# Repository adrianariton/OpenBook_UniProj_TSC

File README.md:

# Ariton Adrian TSC - proiect

# Implementation Steps

1. **Schematic Creation**
2. **Push to 2D PCB**
3. **Routing**
   - GND plane  
   - Net Class for Power Trails  
   - Custom rules & constraints upload  
   - Routing
4. **3D Models Design from Datasheets**
   - Battery  
   - Screen

---

# Hardware Modules and Components

## ESP32-C6-WROOM-1-N8 – Main Microcontroller
- WiFi 6, Bluetooth 5 LE, RISC-V core  
- Power Supply: 3.3V  
- Communications: SPI, I2C, UART, GPIO  

## SD Card Module
- Interface: SPI  
- Pins Used:
  - `SS_SD` → IO4  
  - `MOSI` → IO7  
  - `MISO` → IO2  
  - `SCK` → IO6  

## E-Paper Display
- Interface: SPI  
- Pins Used:
  - `EPD_CS` → IO10  
  - `EPD_DC` → IO5  
  - `EPD_RST` → IO23  
  - `EPD_BUSY` → IO3 (shared with MISO)  
  - MOSI, SCK (shared with SD)

## RTC Module - DS3231SN
- Interface: I2C  
- Pins Used:
  - `SCL` → IO22  
  - `SDA` → IO21  
  - `INT_RTC` → IO8  
  - `32KHZ` → IO1  
  - `RTC_RST` → IO18  

## Environmental Sensor - BME688
- Interface: I2C (shared with RTC)  
- Power Supply: 3.3V  

## External Flash - NORFlash64MB
- Interface: SPI  
- Pins Used:
  - `FLASH_CS` → IO12  
  - Rest (MOSI, MISO, SCK) shared  

## SD/USB Interface
- `USB_D+` → IO13  
- `USB_D-` → IO12  

## Reset and Boot Buttons
- `IO/BOOT` → IO9  
- `RESET` → EN  

## Li-Po Battery Charging Controller
- TP4056 or similar  
- Built-in charging control  
- Battery level monitoring with:
  - Battery ChargeLevel IC → I2C (IO19, IO20)

## Qwiic / Stemma QT Connector
- Communicates entirely via I2C  

## SPI ESD Protection Lines
- Protects the SPI lines for the SD card, e-paper, external flash  

## LDO Voltage Regulator
- Steps down 5V to 3.3V for ESP32-C6 and modules  

## Diodes
- For reverse polarity protection  

## USB-C Connector + ESD Protection
- Main power and data input  
- TVS diodes for ESD protection  

---

# 📊 Block Diagram: Schematic Design

```
+----------------+                                  +--------------------+
| USB C connector|                                  |      Buttons       |
|                |                                  |(Reset, Change, Boot|
+-------+--------+                                  |        IOs)        |
        |                                           +----------+---------+
        |                                                      |
+-------+--------+                                             |
|Battery Charging|                                             |
|  Controller    |-----------+                                   | USB
|   MCP73831     |           |                      +----------+---------+
+-------+--------+           |                      |                    |
        |                    |                      |                    |
        |          +----------------+    3v3 power  |                    |      +----------+
        |          |Voltage Regulator+------------->|                    |      |  SD Card  |
        |          |XC6220A331MR-G  |               |                    +----->|           |
        |          +--------+-------+               |                    |  SPI |    3v3    |
        |                   |                       |      ESP 32        |      +----------+
        |                   |                       |                    |
+-------+--------+          |                       |                    |      +----------+
|                |          |                       |        3v3         |      |NOR Flash  |
|     Battery    +----------+                       |                    +----->|           |
|                |                                  |                    |      |    3v3    |
+-------+--------+                                  |                    |      +----------+
        |                                           |                    |
        |                                           |                    |      +----------+
        |                    I2C                    |                    |      | Display   |
        |         +-------------+------------+------+                    +----->|           |
        |         |             |            |      +----------+---------+      |    3v3    |
        |   +----------+        |        +----------+          |                +----------+
        |   |          |        |        |          |          |         
        +---+ Battery  |  +-----+-----+  | BME688   |  +--------------+   
            | Level    |  |Real Time  |  | Sensor   |  | Stemma QT    |   
            |          |  |  Clock    |  |          |  |              |   
            |          |  |           |  |          |  |     3v3      |   
            +----------+  +-----------+  +----------+  +--------------+   

```

BOM:
Piece Name |	Piece Type (Optional) |	Link
--|--|--|
ESP32-CAP C0402 	|C |	https://componentsearchengine.com/part-view/CC0402MRX5R5BB106/YAGEO
ADAFRUIT_CHIP-LED0603 |	LED |	https://www.snapeda.com/parts/KP-1608SURCK/Kingbright/view-part/?ref=search&t=LED%200603
112ATAARR03 |	microSD |	https://www.snapeda.com/parts/112A-TAAR-R03/Attend/view-part/
744043680 |	L |	https://eu.mouser.com/ProductDetail/Wurth-Elektronik/744043680?qs=PGXP4M47uW6VkZq%252BkzjrHA%3D%3D
BD5229G-TR |	Voltage Detector |	https://www.snapeda.com/parts/BD5229G-TR/Rohm/view-part/?ref=search&t=BD5229G-TR
BUTTON_CUSYOMV1 |	Button |	https://www.snapeda.com/search/?q=EVQP7L01P&search-type=parts
CPH3225A |	C |	https://www.snapeda.com/parts/CPH3225A/Seiko/view-part/
DS3231SN# |	I²C-Integrated RTC/TCXO/Crystal |	https://www.snapeda.com/parts/DS3231SN%23/Analog%20Devices/view-part/?ref=search&t=DS3231SN%23
ESP32-C6-WROOM-1-N8 |	ESP32 |	https://www.snapeda.com/parts/ESP32-C6-WROOM-1-N8/Espressif%20Systems/view-part/?ref=search&t=ESP32-C6-WROOM-1-N8
ESP VARSISTOR |	Varsistor (B72520T0350K062) |	https://ro.mouser.com/ProductDetail/EPCOS-TDK/B72520T0350K062?qs=dEfas%2FXlABIszF52uu7vrg%3D%3D
ESP32_WROVER_AVX---SD0805S020S1R0 |	DIODE SCHOTTKY |	https://componentsearchengine.com/part-view/SD0805S020S1R0/Kyocera%20AVX
ESP32_WROVER_BME680_BME680 |	Env Senzor |	https://www.snapeda.com/parts/BME680/Bosch%20Sensortec/view-part/?ref=search&t=bme680
ESP32_WROVER_EAGLE-LTSPICE_R |	R |	https://componentsearchengine.com/part-view/R0402%201%25%20100%20K%20(RC0402FR-07100KL)/YAGEO
ESP32_WROVER_SPARKFUN-DISCRETESEMI_MOSFET_PCH |	T DMG2305UX-7 |	https://componentsearchengine.com/part-view/DMG2305UX-7/Diodes%20Incorporated
ESP32_WROVER_SPARKFUN-IC-POWER_MCP73831 |	TINY INTEGRATED LI-ION/LI-POLY CHARGE MGNT CONTROLLER |	https://componentsearchengine.com/part-view/MCP73831T-2ACI%2FOT/Microchip
FH34SRJ-24S-0.5SH_99_ |	FH34SRJ-24S-0.5SH(99) |	https://componentsearchengine.com/part-view/FH34SRJ-24S-0.5SH(99)/Hirose
MAX17048G+T10 |	Cell Fuel Gauge with ModelGauge |	https://www.snapeda.com/parts/MAX17048G+T10/Analog%20Devices/view-part/
MBR0530 |	Diode Schottky |	https://www.snapeda.com/parts/MBR0530/Onsemi/view-part/
PGB1010603MR |	Ipp Tvs Diode Surface Mount 0603 |	https://www.snapeda.com/parts/PGB1010603MR/Littelfuse/view-part/
QWIIC_CONNECTOR |	PRT-14417 QWIIC_CONNECTOR |	https://www.snapeda.com/parts/PRT-14417/SparkFun/view-part/
RCL_CPOL-EU |	C pol |	https://grabcad.com/library/tantalum-smd-capacitor-type-b-3528-1
SAMACSYS_PARTS_USB4110-GF-A |	USB4110-GF-A |	https://www.snapeda.com/parts/USB4110-GF-A./Global%20Connector%20Technology/view-part/
SJ |	Jumper-SolderPasteJumper3way |	https://grabcad.com/library/solder-jumpers-1
TP |	Test-Pad |	self-made
SI1308EDL-T1-GE3 |	MOSFET Transistor |	https://www.snapeda.com/parts/SI1308EDL-T1-GE3/Vishay/view-part/
USBLC6-2SC6Y |	Ipp Tvs Diode Surface Mount |	https://www.snapeda.com/parts/USBLC6-2SC6Y/STMicroelectronics/view-part/?ref=dk&t=USBLC6-2SC6Y&con_ref=None
W25Q512JVEIQ |	FLASH - NOR Memory |	https://www.snapeda.com/parts/W25Q512JVEIQ/Winbond%20Electronics/view-part/?ref=search&t=W25Q512JVEIQ
XC6220A331MR-G |	Voltage Regulator |	https://ro.mouser.com/ProductDetail/Torex-Semiconductor/XC6220A331MR-G?qs=AsjdqWjXhJ8ZSWznL1J0gg%3D%3D&utm_source=octopart&utm_medium=aggregator&utm_campaign=865-XC6220A331MR-G&utm_content=Torex%20Semiconductor

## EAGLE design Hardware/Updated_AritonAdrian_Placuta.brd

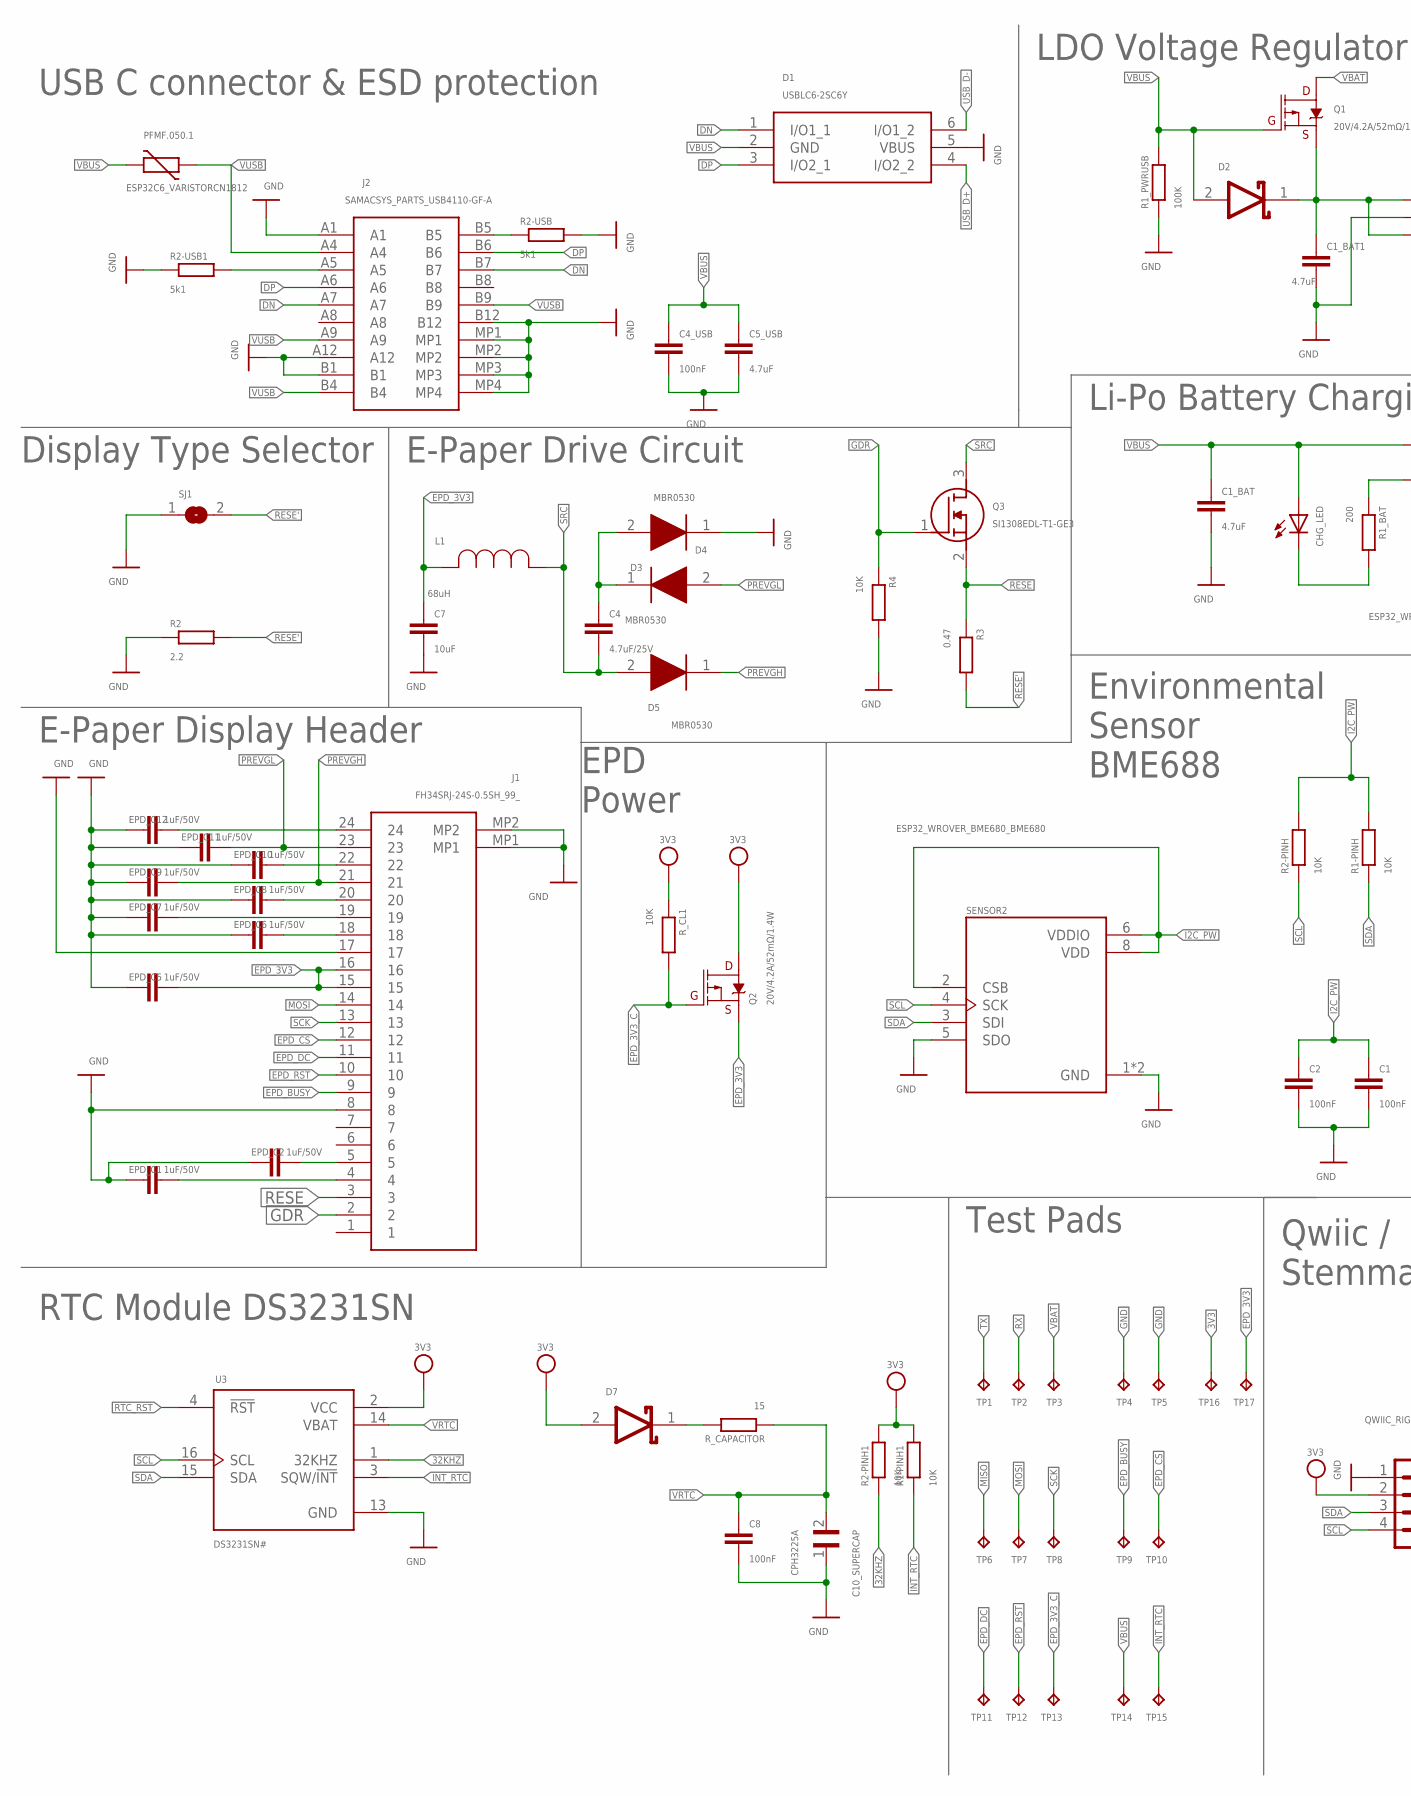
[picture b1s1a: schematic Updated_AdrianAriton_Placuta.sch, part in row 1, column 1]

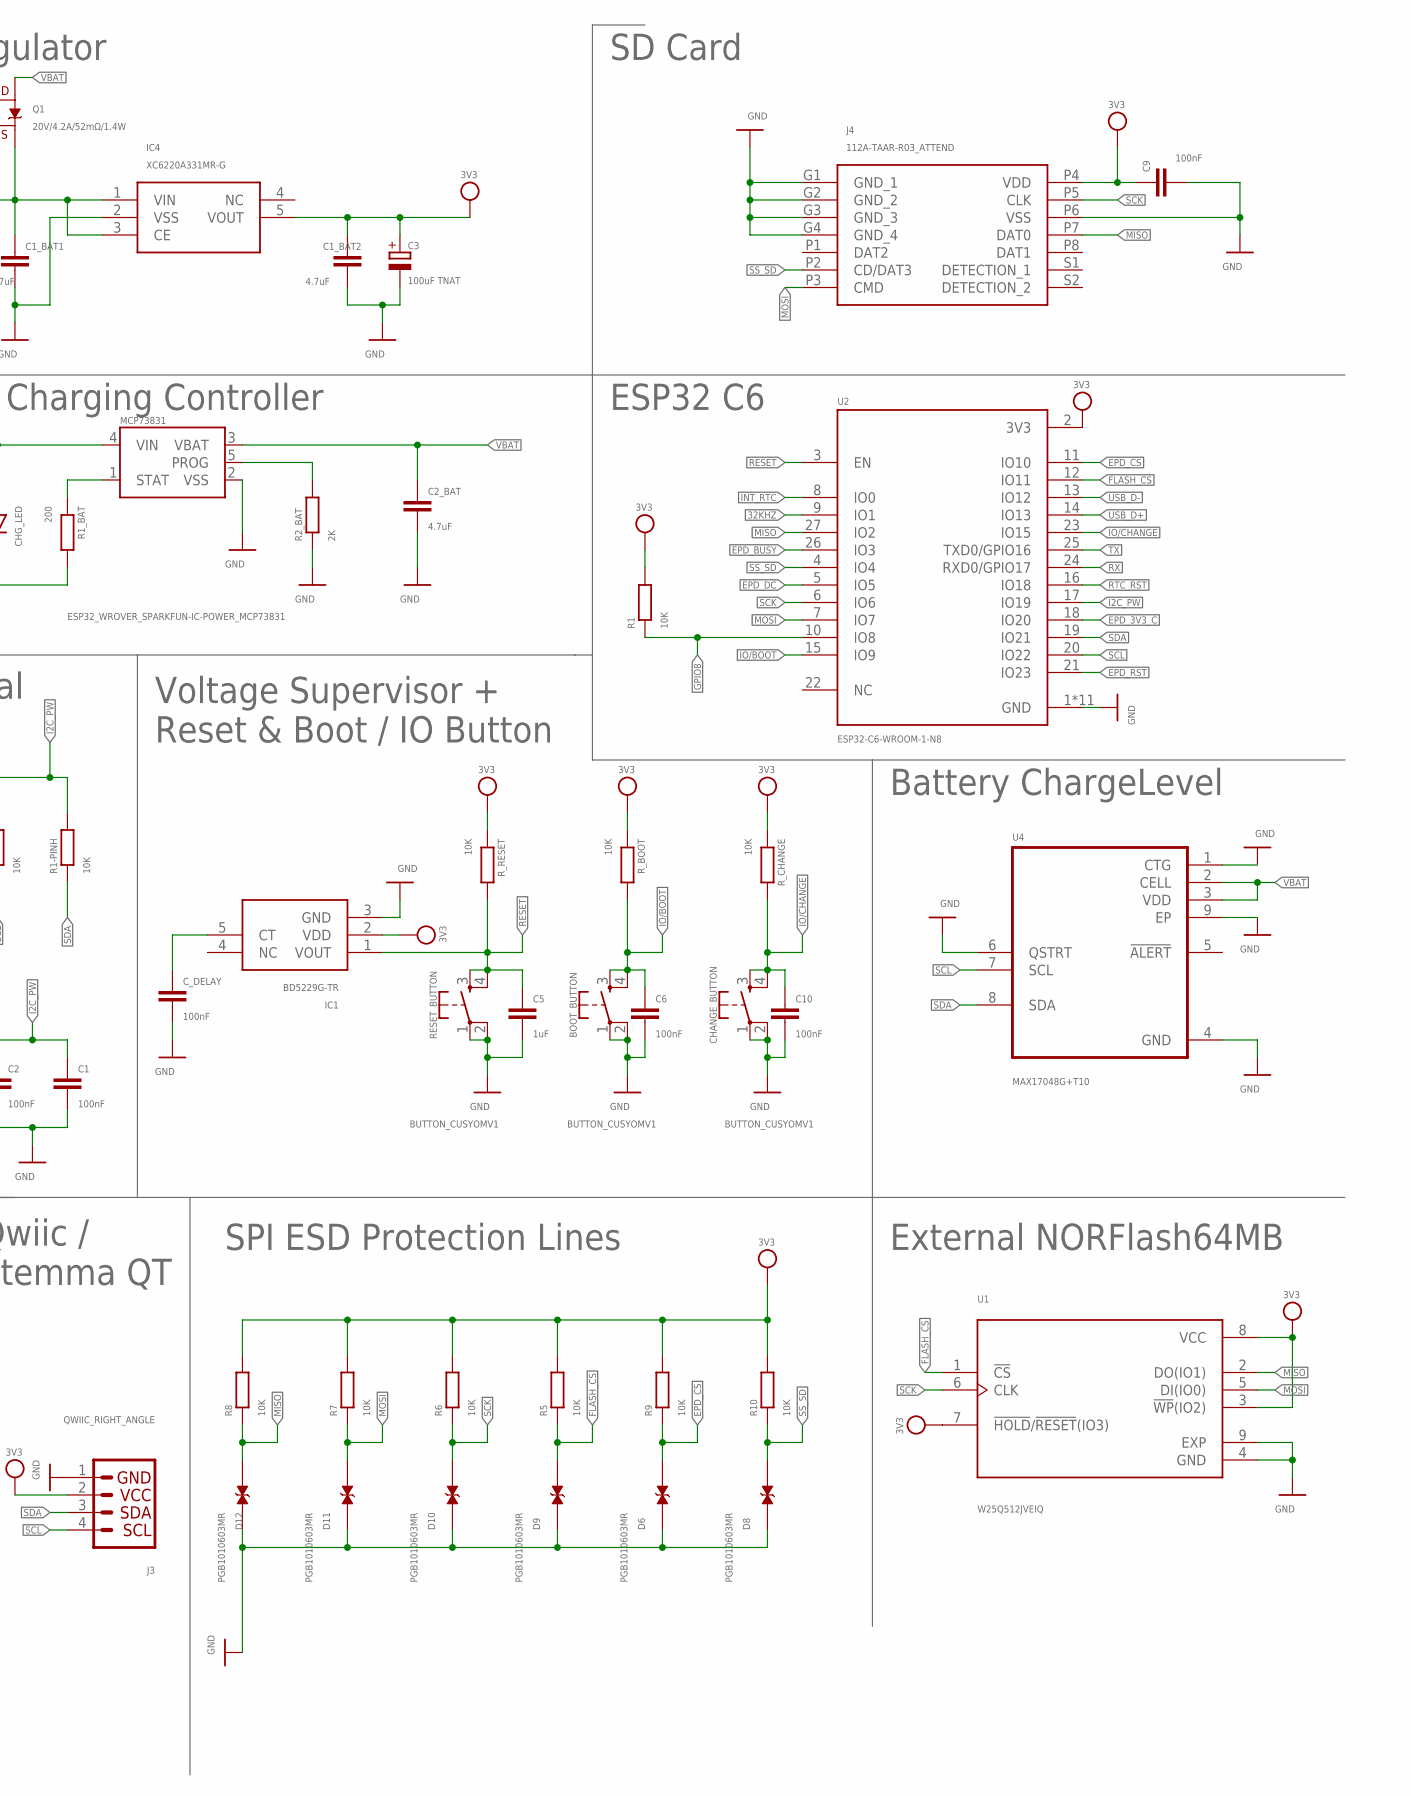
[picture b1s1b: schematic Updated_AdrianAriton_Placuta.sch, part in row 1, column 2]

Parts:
BOOT_BUTTON: BUTTON_CUSYOMV1; MYBUTTON
C1, C2, C6, C8, C9, C10: 100nF; EAGLE-LTSPICE_C0402
C1_BAT, C2_BAT: 4.7uF; EAGLE-LTSPICE_C0402
C1_BAT1, C1_BAT2, C5_USB: 4.7uF; ESP32_WROVER_EAGLE-LTSPICE_C0402
C3: 100uF TNAT; RCL_CT3528
C4: 4.7uF/25V; EAGLE-LTSPICE_C0402
C4_USB: 100nF; ESP32_WROVER_EAGLE-LTSPICE_C0402
C5: 1uF; EAGLE-LTSPICE_C0402
C7: 10uF; EAGLE-LTSPICE_C0402
C10_SUPERCAP: CPH3225A; CAPCP3225X100N
CHANGE_BUTTON: BUTTON_CUSYOMV1; MYBUTTON
CHG_LED: ADAFRUIT_LEDCHIP-LED0603; ADAFRUIT_CHIP-LED0603
C_DELAY: 100nF; EAGLE-LTSPICE_C0402
D1: USBLC6-2SC6Y; SOT95P280X145-6N
D2, D7: ESP32_WROVER_AVX---SD0805S020S1R0_AVX_SD0805S020S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; ESP32_WROVER_AVX---SD0805S020S1R0_AVX_SD0805S020S1R0_0
D3, D4, D5: MBR0530; SOD3716X135N
D6, D8, D9, D10, D11, D12: PGB1010603MR; DIOC1608X36N
EPD_C1, EPD_C2, EPD_C5, EPD_C6, EPD_C7, EPD_C8, EPD_C9, EPD_C10, EPD_C11, EPD_C12: 1uF/50V; EAGLE-LTSPICE_C0402
IC1: BD5229G-TR; SOT95P280X125-5N
IC4: XC6220A331MR-G; SOT95P280X120-5N
J1: FH34SRJ-24S-0.5SH_99_; FH34SRJ24S05SH99
J2: SAMACSYS_PARTS_USB4110-GF-A; SAMACSYS_PARTS_USB4110GFA
J3: QWIIC_RIGHT_ANGLE; JST04_1MM_RA
J4: 112A-TAAR-R03_ATTEND; 112ATAARR03ATTEND
L1: 68uH; IND_4828-WE-TPC_WRE
MCP73831: ESP32_WROVER_SPARKFUN-IC-POWER_MCP73831; SOT95P280X125-5N
PFMF.050.1: ESP32C6_VARISTORCN1812; ESP32C6_VARISTOR_CT/CN1812
Q1, Q2: 20V/4.2A/52mΩ/1.4W; ESP32_WROVER_SPARKFUN-DISCRETESEMI_SOT23-3
Q3: SI1308EDL-T1-GE3; SOT65P210X110-3N
R1, R1-PINH, R1-PINH1, R2-PINH, R2-PINH1, R4, R5, R6, R7, R8, R9, R10: 10K; ESP32_WROVER_EAGLE-LTSPICE_R0402
R1_BAT: 200; ESP32_WROVER_EAGLE-LTSPICE_R0402
R1_PWRUSB: 100K; ESP32_WROVER_EAGLE-LTSPICE_R0402
R2: 2.2; ESP32_WROVER_EAGLE-LTSPICE_R0402
R2-USB, R2-USB1: 5k1; ESP32_WROVER_EAGLE-LTSPICE_R0402
R2_BAT: 2K; ESP32_WROVER_EAGLE-LTSPICE_R0402
R3: 0.47; ESP32_WROVER_EAGLE-LTSPICE_R0402
RESET_BUTTON: BUTTON_CUSYOMV1; MYBUTTON
R_BOOT: 10K; ESP32_WROVER_EAGLE-LTSPICE_R0402
R_CAPACITOR: 15; ESP32_WROVER_EAGLE-LTSPICE_R0402
R_CHANGE: 10K; ESP32_WROVER_EAGLE-LTSPICE_R0402
R_CL1: 10K; ESP32_WROVER_EAGLE-LTSPICE_R0402
R_RESET: 10K; ESP32_WROVER_EAGLE-LTSPICE_R0402
SENSOR2: ESP32_WROVER_BME680_BME680; ESP32_WROVER_BME680_PSON80P300X300X100-8N
SJ1: SJ
TP1, TP2, TP3, TP4, TP5, TP6, TP7, TP8, TP9, TP10, TP11, TP12, TP13, TP14, TP15, TP16, TP17: TPTP20R; TP20R
U1: W25Q512JVEIQ; SON127P600X800X80-9N
U2: ESP32-C6-WROOM-1-N8; XCVR_ESP32-C6-WROOM-1-N8
U3: DS3231SN#; SOIC127P1032X265-16N
U4: MAX17048G+T10; SON50P200X200X80-9N

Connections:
3V3: C1_BAT2.1, C3.+, C9.1, D7.2 (ANODE), IC1.2 (VDD), IC4.5 (VOUT), J3.2, J4.P4 (VDD), Q2.3 (D), R1.2, R1-PINH1.2, R2-PINH1.2, R5.2, R6.2, R7.2, R8.2, R9.2, R10.2, R_BOOT.1, R_CHANGE.1, R_CL1.1, R_RESET.2, TP16.TP, U1.3 (!WP!(IO2)), U1.7 (!HOLD!/!RESET!(IO3)), U1.8 (VCC), U2.2 (3V3), U3.2 (VCC)
32KHZ: R2-PINH1.1, U2.9 (IO1), U3.1 (32KHZ)
DN: D1.1 (I/O1_1), J2.A7, J2.B7
DP: D1.3 (I/O2_1), J2.A6, J2.B6
EPD_3V3: C7.1, EPD_C5.1, J1.15, J1.16, L1.2, Q2.2 (S), TP17.TP
EPD_3V3_C: Q2.1 (G), R_CL1.2, TP13.TP, U2.18 (IO20)
EPD_BUSY: J1.9, TP9.TP, U2.26 (IO3)
EPD_CS: D6.2, J1.12, R9.1, TP10.TP, U2.11 (IO10)
EPD_DC: J1.11, TP11.TP, U2.5 (IO5)
EPD_RST: J1.10, TP12.TP, U2.21 (IO23)
FLASH_CS: D9.2, R5.1, U1.1 (!CS), U2.12 (IO11)
GDR: J1.2, Q3.1 (G), R4.1
GND: BOOT_BUTTON.1, BOOT_BUTTON.2, C1.2, C1_BAT.2, C1_BAT1.2, C1_BAT2.2, C2.2, C2_BAT.2, C3.-, C4_USB.2, C5.2, C5_USB.2, C6.2, C7.2, C8.2, C9.2, C10.2, C10_SUPERCAP.1, CHANGE_BUTTON.1, CHANGE_BUTTON.2, C_DELAY.2, D1.5 (VBUS), D3.1 (K), D6.1, D8.1, D9.1, D10.1, D11.1, D12.1, EPD_C1.2, EPD_C2.2, EPD_C5.2, EPD_C6.2, EPD_C7.2, EPD_C8.2, EPD_C9.2, EPD_C10.2, EPD_C11.2, EPD_C12.2, IC1.3 (GND), IC4.2 (VSS), J1.8, J1.17, J1.MP1, J1.MP2, J2.A1, J2.A12, J2.B1, J2.B12, J2.MP1, J2.MP2, J2.MP3, J2.MP4, J3.1, J4.G1 (GND_1), J4.G2 (GND_2), J4.G3 (GND_3), J4.G4 (GND_4), J4.P6 (VSS), MCP73831.2 (VSS), R1_PWRUSB.1, R2.1, R2-USB.2, R2-USB1.1, R2_BAT.1, R4.2, RESET_BUTTON.1, RESET_BUTTON.2, SENSOR2.1 (GND), SENSOR2.5 (SDO), SENSOR2.7 (GND), SJ1.1, TP4.TP, TP5.TP, U1.4 (GND), U1.9 (EXP), U2.1 (GND), U2.28 (GND), U2.29_1 (GND), U2.29_2 (GND), U2.29_3 (GND), U2.29_4 (GND), U2.29_5 (GND), U2.29_6 (GND), U2.29_7 (GND), U2.29_8 (GND), U2.29_9 (GND), U3.13 (GND), U4.1 (CTG), U4.4 (GND), U4.6 (QSTRT), U4.9 (EP)
GPIO8: R1.1, U2.10 (IO8)
I2C_PW: C1.1, C2.1, R1-PINH.2, R2-PINH.2, SENSOR2.2 (CSB), SENSOR2.6 (VDDIO), SENSOR2.8 (VDD), U2.17 (IO19)
INT_RTC: R1-PINH1.1, TP15.TP, U2.8 (IO0), U3.3 (SQW/!INT)
IO/BOOT: BOOT_BUTTON.3, BOOT_BUTTON.4, C6.1, R_BOOT.2, U2.15 (IO9)
IO/CHANGE: C10.1, CHANGE_BUTTON.3, CHANGE_BUTTON.4, R_CHANGE.2, U2.23 (IO15)
MISO: D12.2, J4.P7 (DAT0), R8.1, TP6.TP, U1.2 (DO(IO1)), U2.27 (IO2)
MOSI: D11.2, J1.14, J4.P3 (CMD), R7.1, TP7.TP, U1.5 (DI(IO0)), U2.7 (IO7)
unnamed: J2.B5, R2-USB.1
unnamed: C1_BAT1.1, D2.1 (CATHODE), IC4.1 (VIN), IC4.3 (CE), Q1.2 (S)
unnamed: MCP73831.1 (STAT), R1_BAT.1
unnamed: J2.A5, R2-USB1.2
unnamed: CHG_LED.C, R1_BAT.2
unnamed: C4.1, D3.2 (A), D4.1 (K)
unnamed: EPD_C12.1, J1.24
unnamed: MCP73831.5 (PROG), R2_BAT.2
unnamed: C_DELAY.1, IC1.5 (CT)
unnamed: EPD_C10.1, J1.22
unnamed: EPD_C8.1, J1.20
unnamed: EPD_C7.1, J1.19
unnamed: EPD_C6.1, J1.18
unnamed: D7.1 (CATHODE), R_CAPACITOR.2
unnamed: EPD_C1.1, J1.4
unnamed: EPD_C2.1, J1.5
PREVGH: D5.1 (K), EPD_C9.1, J1.21
PREVGL: D4.2 (A), EPD_C11.1, J1.23
RESE: J1.3, Q3.2 (S), R3.1
RESE': R2.2, R3.2, SJ1.2
RESET: C5.1, IC1.1 (VOUT), RESET_BUTTON.3, RESET_BUTTON.4, R_RESET.1, U2.3 (EN)
RTC_RST: U2.16 (IO18), U3.4 (!RST)
RX: TP2.TP, U2.24 (RXD0/GPIO17)
SCK: D10.2, J1.13, J4.P5 (CLK), R6.1, TP8.TP, U1.6 (CLK), U2.6 (IO6)
SCL: J3.4, R2-PINH.1, SENSOR2.4 (SCK), U2.20 (IO22), U3.16 (SCL), U4.7 (SCL)
SDA: J3.3, R1-PINH.1, SENSOR2.3 (SDI), U2.19 (IO21), U3.15 (SDA), U4.8 (SDA)
SRC: C4.2, D5.2 (A), L1.1, Q3.3 (D)
SS_SD: D8.2, J4.P2 (CD/DAT3), R10.1, U2.4 (IO4)
TX: TP1.TP, U2.25 (TXD0/GPIO16)
USB_D+: D1.4 (I/O2_2), U2.14 (IO13)
USB_D-: D1.6 (I/O1_2), U2.13 (IO12)
VBAT: C2_BAT.1, MCP73831.3 (VBAT), Q1.3 (D), TP3.TP, U4.2 (CELL), U4.3 (VDD)
VBUS: C1_BAT.1, C4_USB.1, C5_USB.1, CHG_LED.A, D1.2 (GND), D2.2 (ANODE), MCP73831.4 (VIN), PFMF.050.1.2, Q1.1 (G), R1_PWRUSB.2, TP14.TP
VRTC: C8.1, C10_SUPERCAP.2, R_CAPACITOR.1, U3.14 (VBAT)
VUSB: J2.A4, J2.A9, J2.B4, J2.B9, PFMF.050.1.1

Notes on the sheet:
USB C connector & ESD protection
LDO Voltage Regulator
SD Card
Display Type Selector
E-Paper Drive Circuit
Li-Po Battery Charging Controller
ESP32 C6
E-Paper Display Header
EPD Power
Environmental Sensor BME688
Voltage Supervisor + Reset & Boot / IO Button
Battery ChargeLevel
RTC Module DS3231SN
Test Pads
Qwiic / Stemma QT
SPI ESD Protection Lines
External NORFlash64MB

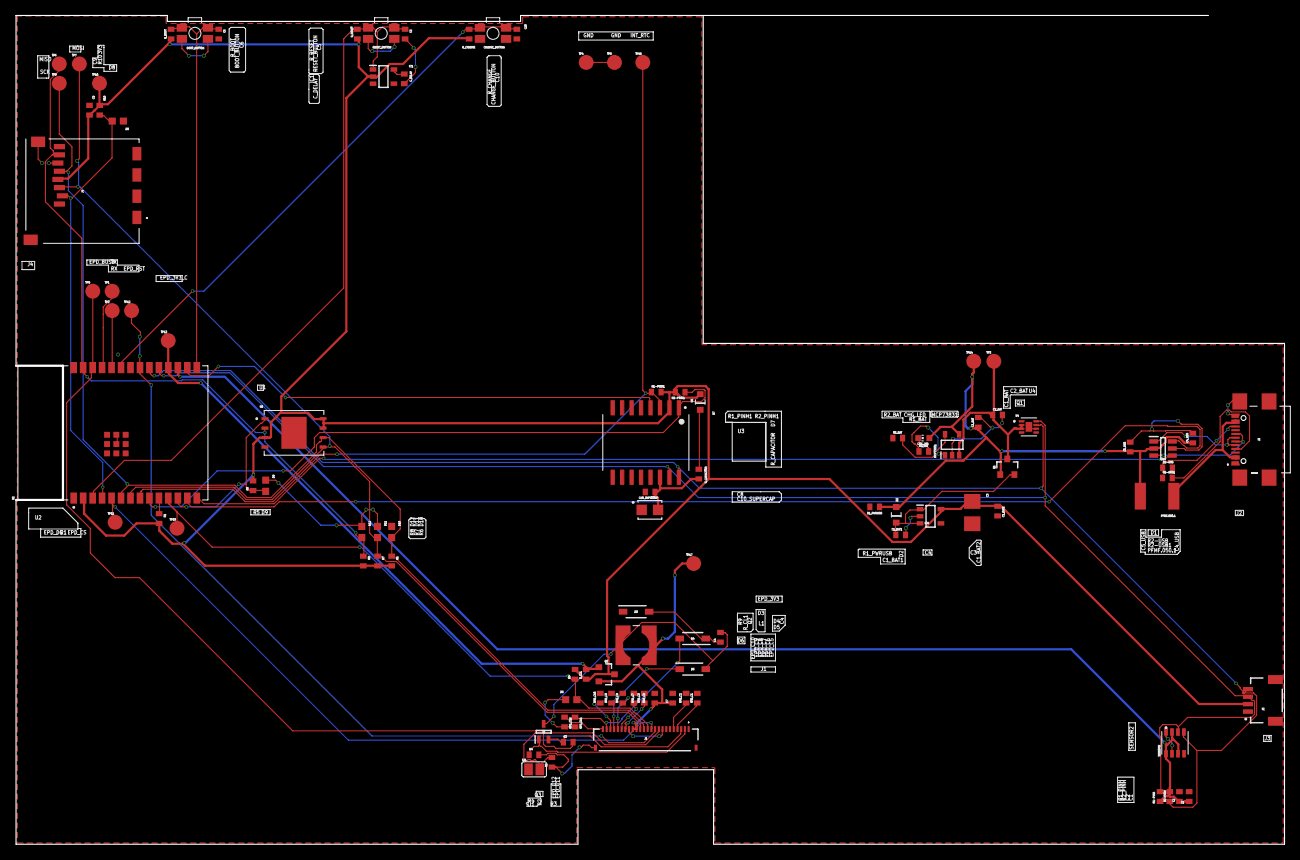
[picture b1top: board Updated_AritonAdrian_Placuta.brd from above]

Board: 2 copper layers, 170.2 x 111.2 mm, 103 parts (0 on the bottom side), 55 nets.

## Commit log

2025-04-05 added files
2025-04-05 added link file
2025-04-14 fixed issues

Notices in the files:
parts and their libraries:
DeskAssistant v19 v1: COPYRIGHT: Copyright (C) 2024 Ultra Librarian. All rights reserved.
